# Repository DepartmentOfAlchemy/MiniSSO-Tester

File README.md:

# MiniSSO-Tester
Tester for the MiniSSO board.

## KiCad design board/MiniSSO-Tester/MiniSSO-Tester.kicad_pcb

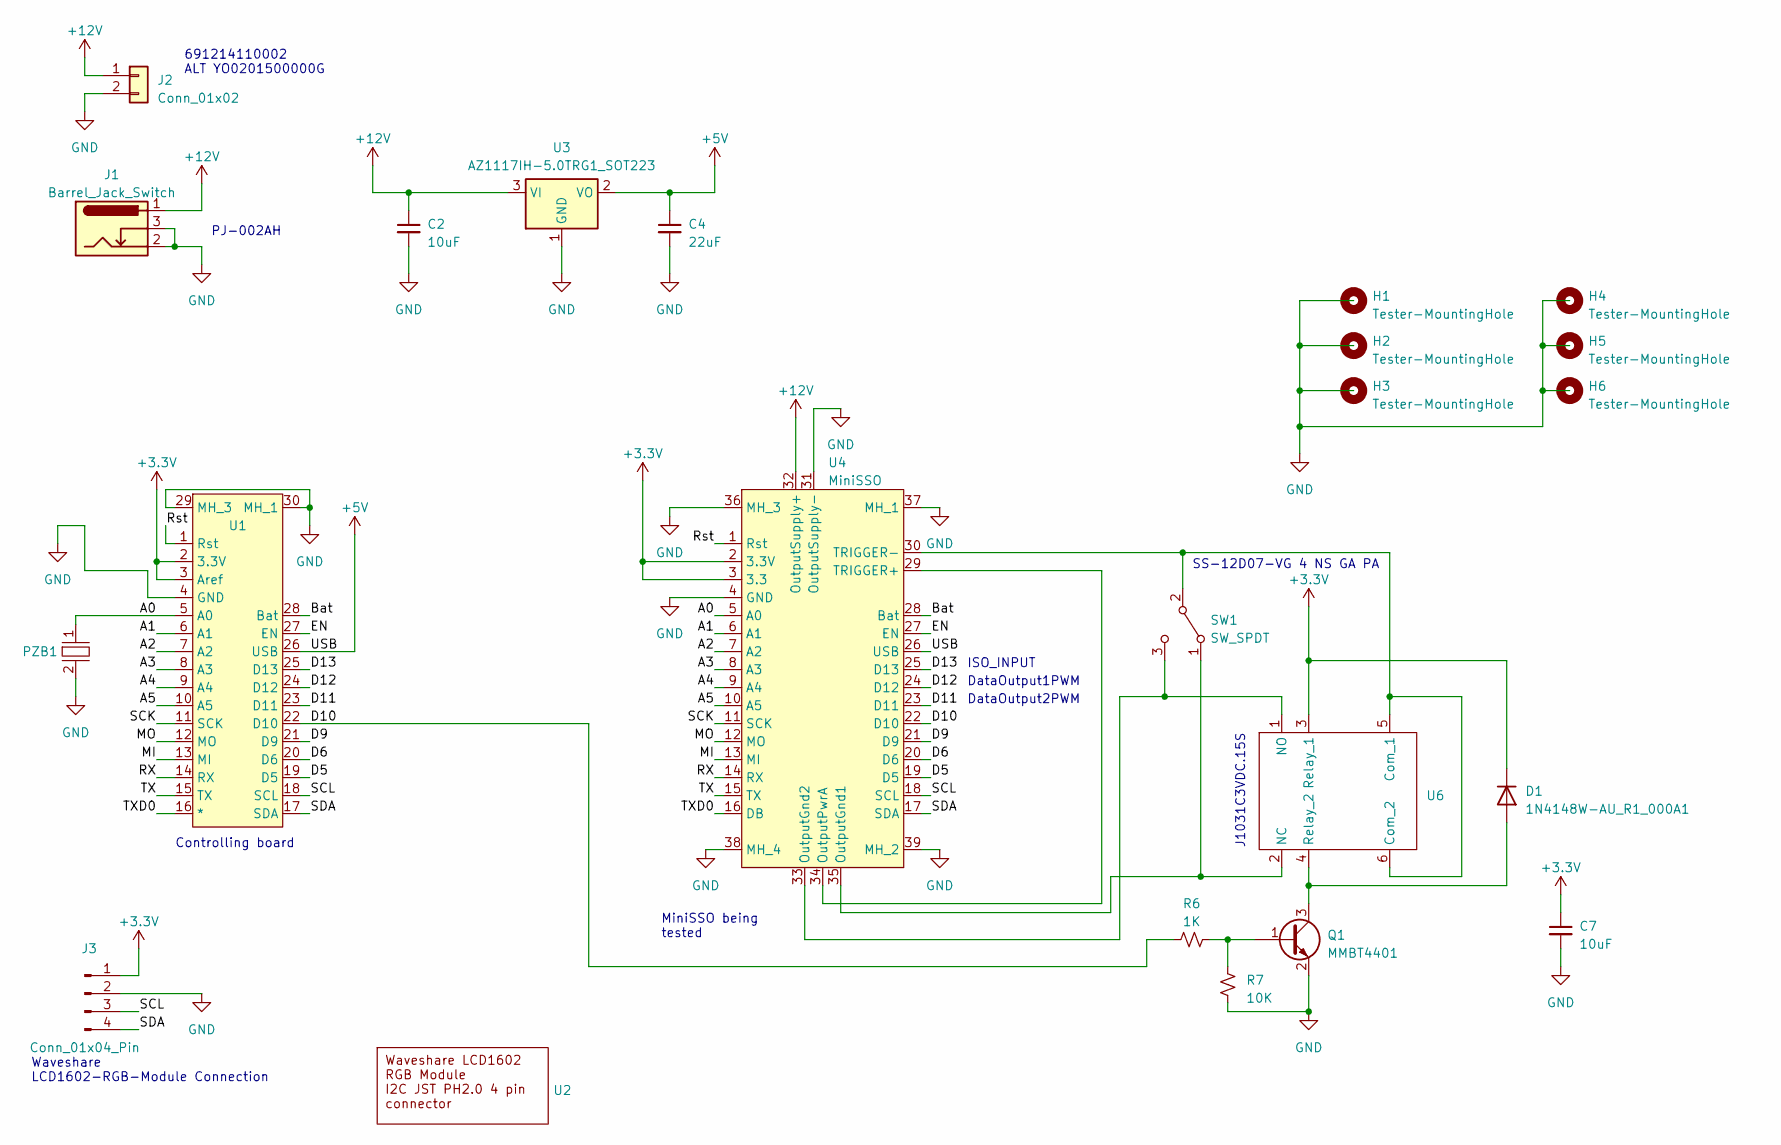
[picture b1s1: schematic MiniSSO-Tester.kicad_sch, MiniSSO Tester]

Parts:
C2, C7: 10uF; C_0603_1608Metric_Pad1.08x0.95mm_HandSolder
C4: 22uF; C_0603_1608Metric_Pad1.08x0.95mm_HandSolder
D1: 1N4148W-AU_R1_000A1; D_SOD-123
H1, H2, H3, H4, H5, H6: Tester-MountingHole; MountingHole_2.7mm_M2.5_ISO14580
J1: Barrel_Jack_Switch; BarrelJack_Kycon_KLDX-0202-xC_Horizontal
J2: Conn_01x02; 691214110002
J3: Conn_01x04_Pin; PinHeader_1x04_P2.54mm_Vertical
PZB1: Buzzer_TDK_PS1240P02BT_D12.2mm_H6.5mm
Q1: MMBT4401; SOT-23
R6: 1K; R_0603_1608Metric_Pad0.98x0.95mm_HandSolder
R7: 10K; R_0603_1608Metric_Pad0.98x0.95mm_HandSolder
SW1: SW_SPDT; SW_Slide_1P2T_CK_OS102011MS2Q
U1: Feather Pins
U2: Waveshare-19537-LCD1602-RGB
U3: AZ1117IH-5.0TRG1_SOT223; SOT-223-3_TabPin2
U4: MiniSSO; MiniSSO-ThroughHole
U6: Relay_SPDT_HsinDa_Y14

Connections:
+3.3V: C7.1, D1.1 (K), J3.1, U1.2 (3.3V), U1.3 (Aref), U4.2 (3.3V), U4.3 (3.3), U6.3 (Relay_1)
+5V: C4.1, U1.26 (USB), U3.2 (VO), U4.26 (USB)
+12V: C2.1, J1.1, J2.1, U3.3 (VI), U4.32 (OutputSupply+)
/A0: PZB1.1, U1.5 (A0), U4.5 (A0)
/A1: U1.6 (A1), U4.6 (A1)
/A2: U1.7 (A2), U4.7 (A2)
/A3: U1.8 (A3), U4.8 (A3)
/A4: U1.9 (A4), U4.9 (A4)
/A5: U1.10 (A5), U4.10 (A5)
/Bat: U1.28 (Bat), U4.28 (Bat)
/D5: U1.19 (D5), U4.19 (D5)
/D6: U1.20 (D6), U4.20 (D6)
/D9: U1.21 (D9), U4.21 (D9)
/D10: R6.1, U1.22 (D10), U4.22 (D10)
/D11: U1.23 (D11), U4.23 (D11)
/D12: U1.24 (D12), U4.24 (D12)
/D13: U1.25 (D13), U4.25 (D13)
/EN: U1.27 (EN), U4.27 (EN)
/MI: U1.13 (MI), U4.13 (MI)
/MO: U1.12 (MO), U4.12 (MO)
/RX: U1.14 (RX), U4.14 (RX)
/Rst: U1.1 (Rst), U4.1 (Rst)
/SCK: U1.11 (SCK), U4.11 (SCK)
/SCL: J3.3, U1.18 (SCL), U4.18 (SCL)
/SDA: J3.4, U1.17 (SDA), U4.17 (SDA)
/TX: U1.15 (TX), U4.15 (TX)
/TXD0: U1.16 (*), U4.16 (DB)
GND: C2.2, C4.2, C7.2, J1.2, J1.3, J2.2, J3.2, PZB1.2, Q1.2 (E), R7.2, U1.4 (GND), U1.29 (MH_3), U1.30 (MH_1), U3.1 (GND), U4.4 (GND), U4.31 (OutputSupply-), U4.36 (MH_3), U4.37 (MH_1), U4.38 (MH_4), U4.39 (MH_2)
unnamed: D1.2 (A), Q1.3 (C), U6.4 (Relay_2)
unnamed: Q1.1 (B), R6.2, R7.1
unnamed: SW1.1 (A), U4.35 (OutputGnd1), U6.2 (NC)
unnamed: SW1.2 (B), U4.30 (TRIGGER-), U6.5 (Com_1), U6.6 (Com_2)
unnamed: SW1.3 (C), U4.33 (OutputGnd2), U6.1 (NO)
unnamed: U4.29 (TRIGGER+), U4.34 (OutputPwrA)

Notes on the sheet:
J1031C3VDC.15S
PJ-002AH
DataOutput1PWM
Controlling board
ISO_INPUT
DataOutput2PWM
SS-12D07-VG 4 NS GA PA
691214110002 ALT YO0201500000G
MiniSSO being tested
Waveshare LCD1602-RGB-Module Connection

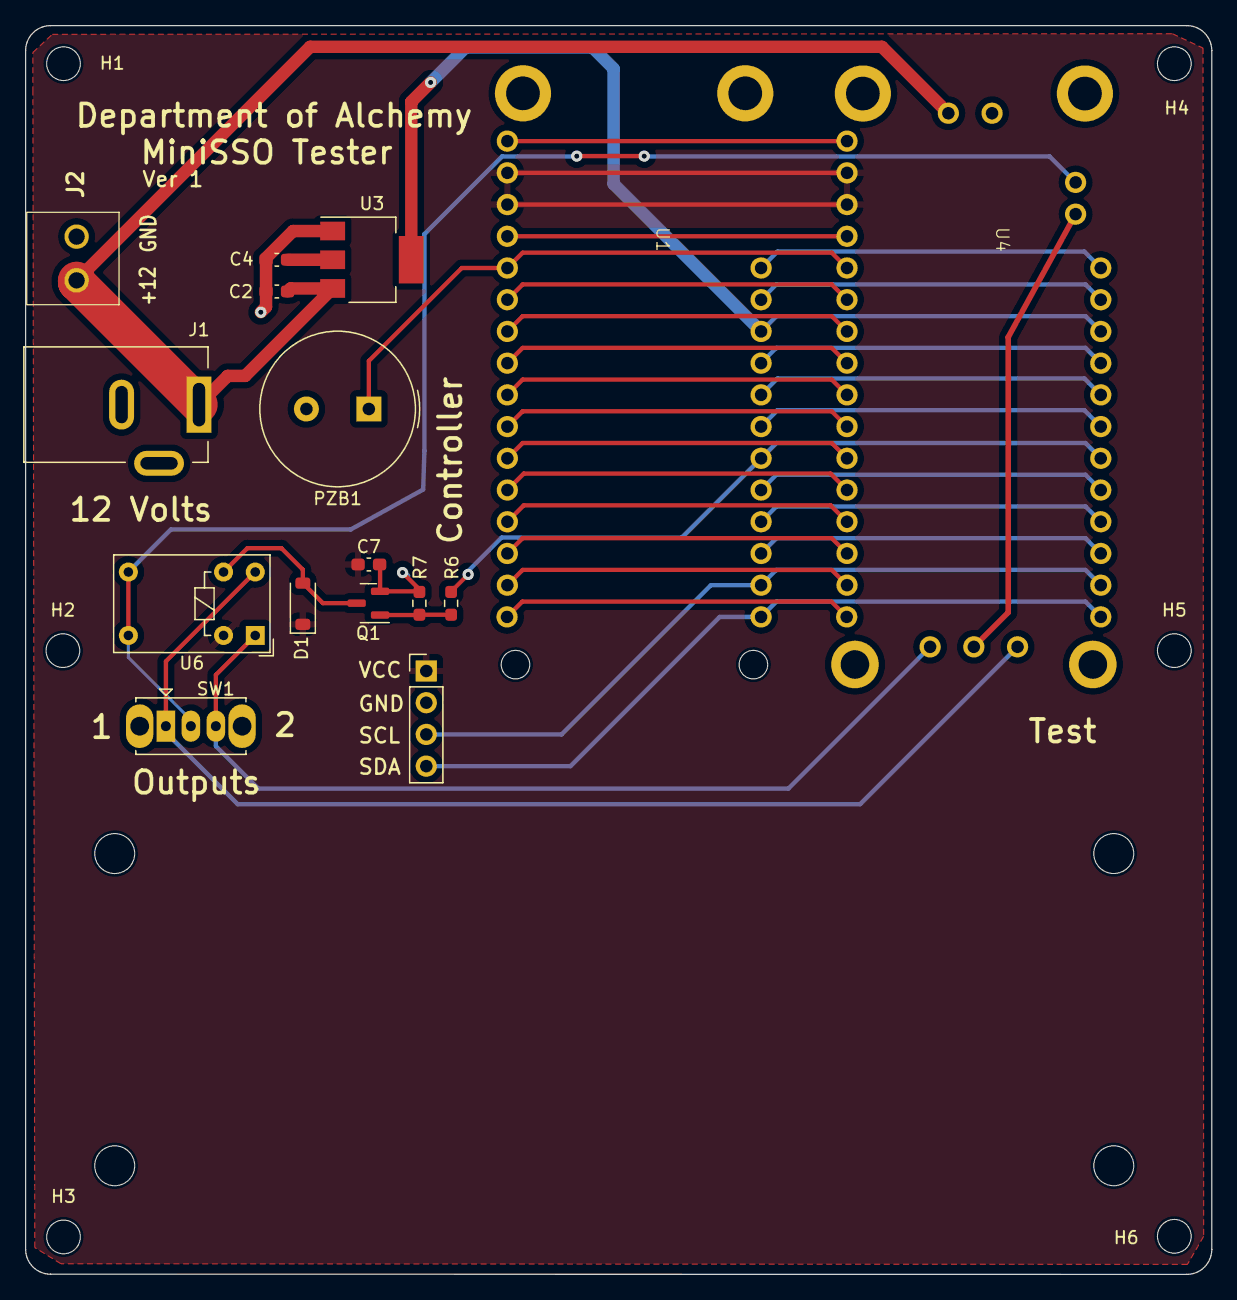
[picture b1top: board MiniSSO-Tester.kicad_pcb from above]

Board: 2 copper layers, 95.0 x 100.0 mm, 23 parts (0 on the bottom side), 34 nets.

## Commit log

2023-06-13 Revision 1. First commit of the tester board used for the MiniSSO board. The arduino/MiniSSO-Tester/MiniSSO-Tester.ino file is the test code for testing a MiniSSO board with the tester.
